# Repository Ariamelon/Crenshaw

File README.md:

# Crenshaw
1.5" SSD1351 RGB OLED [VIK](https://github.com/sadekbaroudi/vik) module.

## Disclaimer
This board is licensed under CERN-OHL-S-2.0.

## VIK module certification card

| Category                | Classification          | Response           |
| ----------------------- | ----------------------- | ------------------ |
| FPC connector           | Required                | :heavy_check_mark: |
| Breakout pins           | Recommended             | :x:                |
| Uses: SPI               | Optional                | :heavy_check_mark: |
| SPI used for SPI only   | Strongly recommended    | :heavy_check_mark: |
| Uses: I2C               | Optional                | :x:                |
| I2C used for I2C only   | Strongly Recommended    | N/A                |
| I2C pull ups            | Required                | N/A                |
| Uses: RGB               | Optional                | :x:                |
| Uses: Extra GPIO 1      | Optional                | :heavy_check_mark: |
| Uses: Extra GPIO 2      | Optional                | :heavy_check_mark: |
| Standard PCB Size/Mount | Strongly Recommended    | :x:                |

## Changelog
 * 22/10/2024: License updated to CERN-OHL-S-2.0.
* 04/08/2023: Changed VIK and OLED FFC to FH12. Stitched ground planes together. Fixed VIK footprint. Moved production files to easier to access location.
* 28/07/2023: Added pin labels. Added VIK size row to certification card.
* 27/07/2023: Added voltage regulator, SSD1351 supporting circuitry and [VIK](https://github.com/sadekbaroudi/vik) connector. Added license. Added metadata to schematic and board files. Added VIK module certification card.
* 26/07/2023: Updated to V2.0.
* 11/11/2020: Updated to V1.2. Slightly increased size. Moved ribbon cable connector away from center of board as it was causing issues where it was. Spread components apart to allow for easier soldering.
* 30/09/2020: Updated to V1.1. Fixed orientation of I2C headers, increased silkscreen text size, moved ribbon cable connector further towards center of board.
* 29/09/2020: D1 SOD323 switched to SOD123.
* 27/09/2020: Initial commit.

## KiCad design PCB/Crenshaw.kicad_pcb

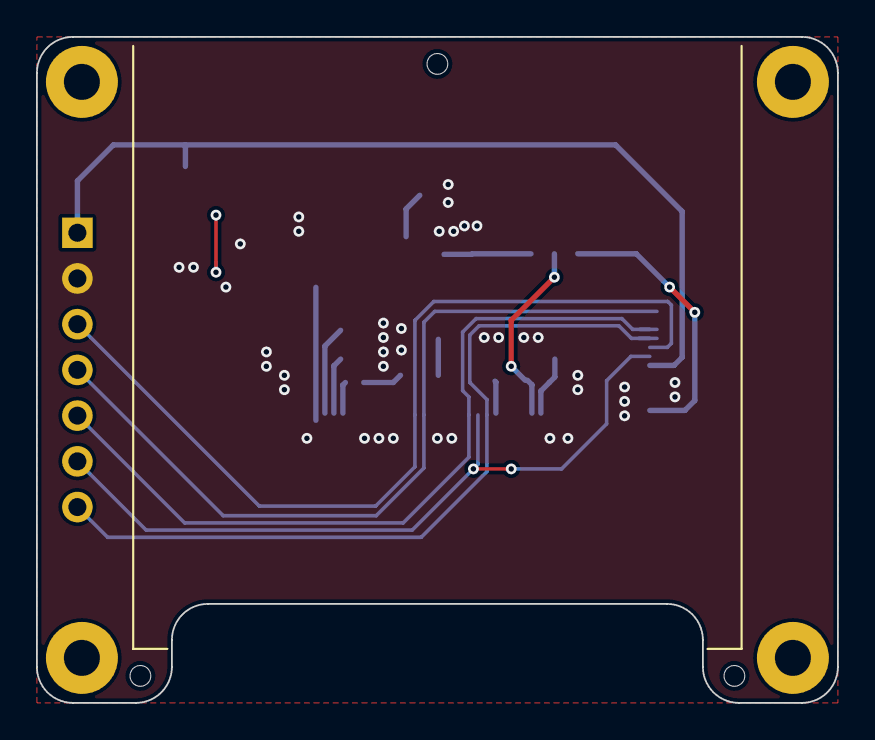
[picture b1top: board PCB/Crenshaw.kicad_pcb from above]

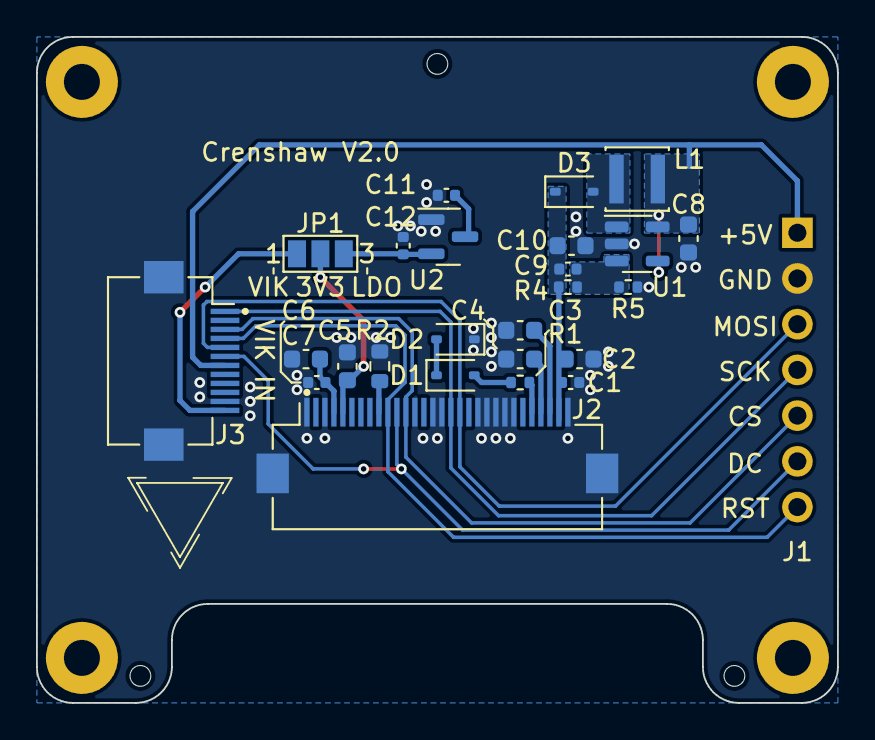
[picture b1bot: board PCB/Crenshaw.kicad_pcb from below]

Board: 2 copper layers, 44.5 x 37.0 mm, 31 parts (27 on the bottom side), 20 nets.

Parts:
A1: Ariamelon Logo; Ariamelon_Logo_x2_Mask
A2: VIK logo; vik-logo-small
C1, C6: 100n; C_0402_1005Metric
C2: 10u; C_0603_1608Metric
C3, C4, C5, C7: 1u; C_0603_1608Metric
C8, C10: 4u7; C_0603_1608Metric
C9: 22p; C_0402_1005Metric
C11, C12: 1u; C_0402_1005Metric
D1, D2: 1N4148; D_SOD-323
D3: 1N5819WS; D_SOD-323
H1, H2, H3: Tooling Hole; JLC Tooling Hole
J1: OLED_Breakout; OLED_1.5_SSD1351_128x128
J2: SSD1351; Hirose_FH12-30S-0.5SH_1x30-1MP_P0.50mm_Horizontal
J3: VIK Module; vik-module-connector-horizontal
JP1: 3V3 SEL; SolderJumper-3_P1.3mm_Open_Pad1.0x1.5mm_NumberLabels
L1: 10u; L_Sunlord_SWPA3012S
R1: 51; R_0402_1005Metric
R2: 560k; R_0603_1608Metric
R4: 1M; R_0402_1005Metric
R5: 100k; R_0402_1005Metric
U1: TPS61040DBV; SOT-23-5
U2: XC6206P332MR; SOT-23

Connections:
+3V3: C5.1, J2.5 (VDD), JP1.2 (C)
+3V3_LDO: C12.1, JP1.3 (B), U2.2 (VO)
+3V3_VIK: J3.12 (3V3), JP1.1 (A)
+5V: C8.2, C11.1, J1.1, J3.7 (5V), L1.2, U1.4 (EN), U1.5 (VIN), U2.3 (VI)
+13V: C1.1, C2.1, C9.2, C10.2, D3.1 (K), J2.29 (VCC), R4.2
CS: J1.5, J2.12 (~CS), J3.3 (CS)
DC: J1.6, J2.11 (D/~C), J3.6 (GPIO1)
GND: C1.2, C2.2, C3.2, C4.2, C5.2, C6.2, C7.2, C8.1, C10.1, C11.2, C12.2, D2.1 (K), J1.2, J2.1 (NC(GND)), J2.3 (VSS), J2.13 (BS1), J2.15 (R/~W), J2.16 (E/~RD), J2.20 (D3), J2.21 (D4), J2.22 (D5), J2.23 (D6), J2.24 (D7), J2.30 (NC(GND)), J2.MP, J3.11 (GND), J3.MP, R2.2, R5.2, U1.2 (GND), U2.1 (GND)
MOSI: J1.3, J2.18 (D1), J3.5 (MOSI)
unnamed: D1.2 (A), R1.1
unnamed: D1.1 (K), D2.2 (A)
unnamed: D3.2 (A), L1.1, U1.1 (SW)
unnamed: J2.9 (IREF), R2.1
unnamed: C6.1, C7.1, J2.4 (VCI)
unnamed: C3.1, J2.28 (VCOMH)
unnamed: C4.1, J2.27 (VDDIO)
unnamed: J2.26 (VSL), R1.2
unnamed: C9.1, R4.1, R5.1, U1.3 (FB)
SCK: J1.4, J2.17 (D0), J3.1 (SCLK)
~RST: J1.7, J2.10 (~RES), J3.4 (GPIO2)

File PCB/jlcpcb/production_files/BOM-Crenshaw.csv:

Comment,Designator,Footprint,LCSC
22p,C9,C_0402_1005Metric,C1555
1u,"C3,C4,C5,C7",C_0603_1608Metric,C15849
1N5819WS,D3,D_SOD-323,C191023
4u7,"C10,C8",C_0603_1608Metric,C19666
10u,L1,L_Sunlord_SWPA3012S,C206385
1N4148,"D1,D2",D_SOD-323,C2128
560k,R2,R_0603_1608Metric,C23203
51,R1,R_0402_1005Metric,C25125
100k,R5,R_0402_1005Metric,C25741
1M,R4,R_0402_1005Metric,C26083
100n,"C1,C6",C_0402_1005Metric,C307331
SSD1351,J2,HRS_FH34SRJ-30S-0.5SH(50),C324727
VIK Module,J3,vik-module-connector-horizontal,C424659
1u,"C11,C12",C_0402_1005Metric,C52923
XC6206P332MR,U2,SOT-23,C5446
TPS61040DBV,U1,SOT-23-5,C7722
10u,C2,C_0603_1608Metric,C96446
OLED_Breakout,J1,OLED_1.5_SSD1351_128x128,

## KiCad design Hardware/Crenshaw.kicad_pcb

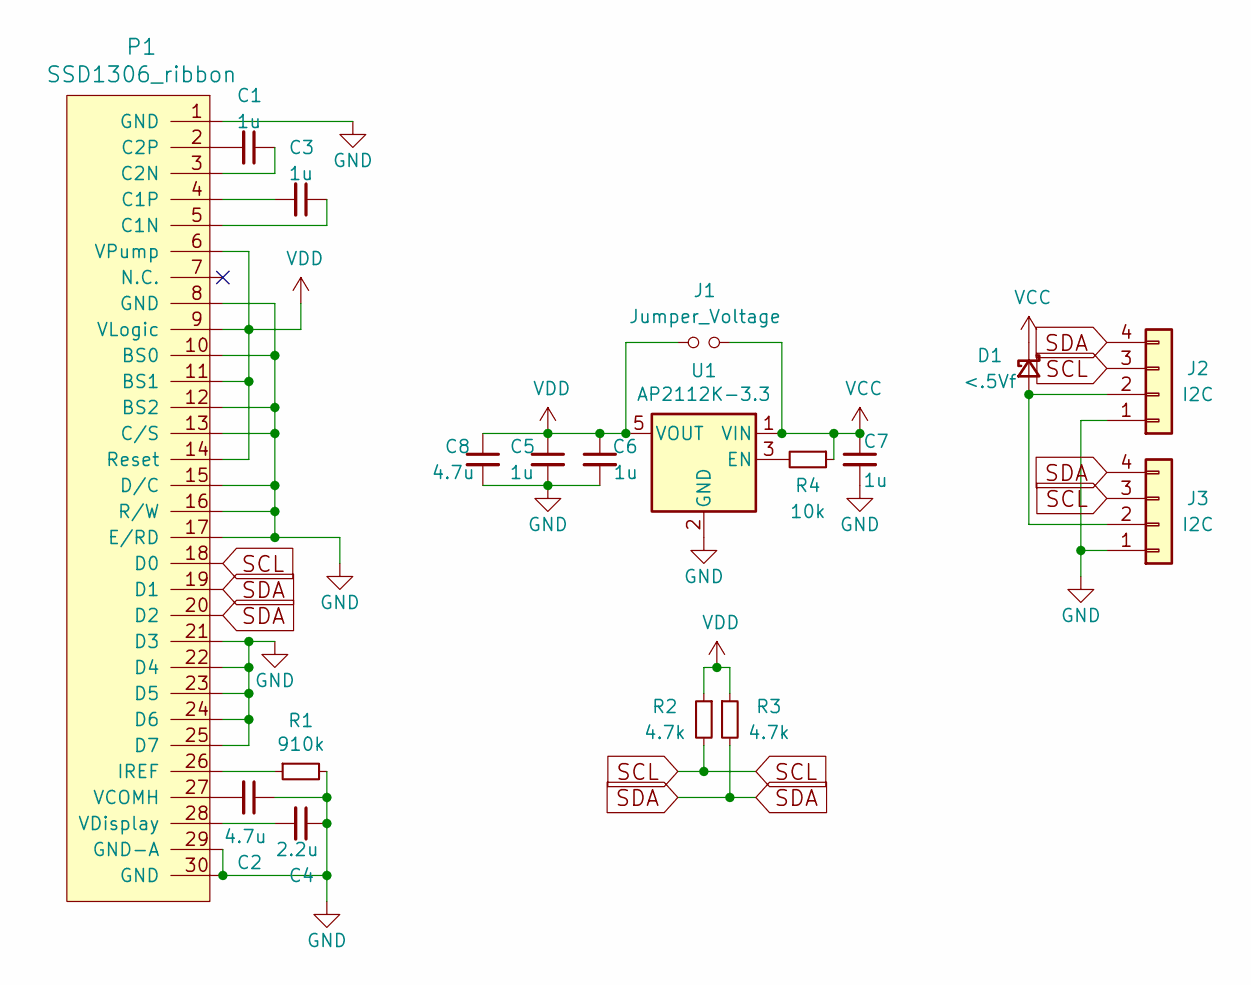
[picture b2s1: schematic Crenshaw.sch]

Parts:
C1, C3, C5, C6, C7: 1u; C_0603_1608Metric
C2, C8: 4.7u; C_0603_1608Metric
C4: 2.2u; C_0603_1608Metric
D1: <.5Vf; D_SOD-123
J1: Jumper_Voltage; SolderJumper-2_P1.3mm_Open_Pad1.0x1.5mm
J2, J3: I2C; PinHeader_1x04_P2.54mm_Vertical_No_Silk
P1: SSD1306_ribbon
R1: 910k; R_0603_1608Metric
R2, R3: 4.7k; R_0603_1608Metric
R4: 10k; R_0603_1608Metric
U1: AP2112K-3.3; SOT-23-5

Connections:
GND: C2.1, C4.1, C5.2, C6.2, C7.2, C8.2, J2.1, J3.1, P1.1 (GND), P1.8 (GND), P1.10 (BS0), P1.12 (BS2), P1.13 (C/S), P1.15 (D/C), P1.16 (R/W), P1.17 (E/RD), P1.21 (D3), P1.22 (D4), P1.23 (D5), P1.24 (D6), P1.25 (D7), P1.29 (GND-A), P1.30 (GND), R1.2, U1.2 (GND)
unnamed: C1.1, P1.3 (C2N)
unnamed: C1.2, P1.2 (C2P)
unnamed: C2.2, P1.27 (VCOMH)
unnamed: C3.1, P1.5 (C1N)
unnamed: C3.2, P1.4 (C1P)
unnamed: C4.2, P1.28 (VDisplay)
unnamed: D1.2 (A), J2.2, J3.2
unnamed: P1.26 (IREF), R1.1
unnamed: R4.2, U1.3 (EN)
SCL: J2.3, J3.3, P1.18 (D0), R2.2
SDA: J2.4, J3.4, P1.19 (D1), P1.20 (D2), R3.2
VCC: C7.1, D1.1 (K), J1.1, R4.1, U1.1 (VIN)
VDD: C5.1, C6.1, C8.1, J1.2, P1.6 (VPump), P1.9 (VLogic), P1.11 (BS1), P1.14 (Reset), R2.1, R3.1, U1.5 (VOUT)

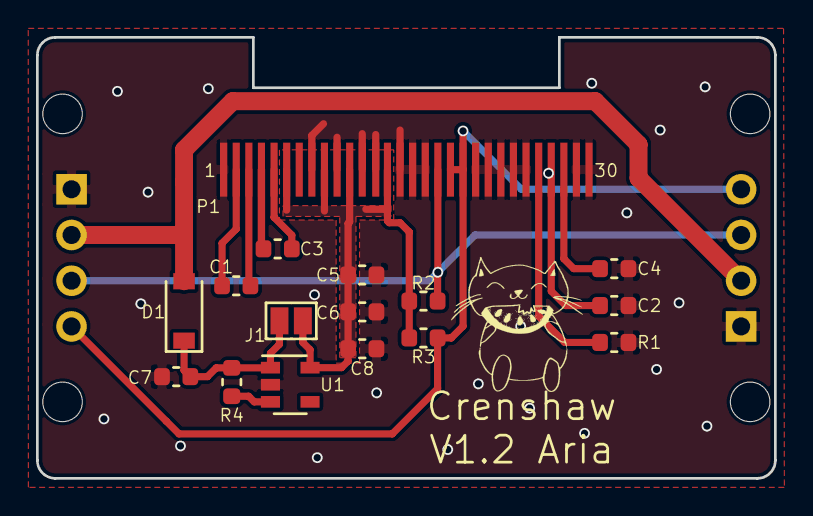
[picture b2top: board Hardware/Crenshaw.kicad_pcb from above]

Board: 2 copper layers, 41.0 x 24.5 mm, 18 parts (0 on the bottom side), 14 nets.

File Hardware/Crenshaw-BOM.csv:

Name,Component,Package,Value,Qty
"C1, C3, C5-C7",Capacitor,0603,1uF,5
"C2, C8",Capacitor,0603,4.7uF,2
D1,Schottky,SOD-123,<.5VF,1
P1,OLED,"1.3""",SSD1306,1
R1,Resistor,0603,910k,1
"R2, R3",Resistor,0603,4.7k,2
U1,3.3v LDO,SOT23-5,XC6220B331MR-G,1

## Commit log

2020-09-28 Added link to Hami numpad
2020-09-28 Added Gerber files
2020-09-28 Added BOM
2020-09-29 SOD323 schottky switched to SOD123
    Bigger means less heat issues
2020-09-30 Create LICENSE
2020-09-30 Updated to V1.1 - fixed several major errors
    Fixed issue with orientation of I2C headers, increased size of silkscreen text, and moved ribbon cable connector lower down the board.
2020-10-01 Added renders and updated readme
2020-10-01 Fixed broken link oops
2020-10-02 Updated BOM
2020-10-24 Better render
2020-10-26 Added photo
2020-10-26 Added video
2020-11-10 Updated to V1.2
2023-07-26 V2.0 released
    Now an adapter board for the SSD1351 that is just a 1 to 1 FFC cable adapter.
2023-07-27 27/03/2023 update
    Added voltage regulator, SSD1351 supporting circuitry and [VIK](https://github.com/sadekbaroudi/vik) connector. Added license. Added metadata to schematic and board files. Added VIK module certificat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
2023-07-28 28/07/2023 update
    Added pin labels. Added VIK size row to certification card.
2023-08-04 04/08/2023 update
    Changed VIK and OLED FFC to FH12. Stitched ground planes together. Fixed VIK footprint. Moved production files to easier to access location.
2024-10-22 License updated to CERN-OHL-S-2.0.

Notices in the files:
PCB/Crenshaw.kicad_pcb:
Licensed under CC BY 4.0.
